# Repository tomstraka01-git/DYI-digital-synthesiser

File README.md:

# DYI digital synthesiser

## What is it?
It is a digital synthesizer fully made by me. It has 4 buttons and 5 controllable analog knobs to change settings. It can produce polyphonic sound and can connect to midi. It has settings like frequency, detune, volume, filters, chorus, delay, lfo, etc. It has two 2 watt speakers to produce sound and fully made by me pcb.

## Why?
I have always liked music, since i was kid i played piano, so i wanted to connect my interest in electronics and music into one project. That is why i  made this synthesizer. It has taught me about digital sound and audio alot.

## Electronics
The project uses custom pcb and some modules. It uses PCM5102 I2S audio module for sound generation and PAM8403 for sound amplifying, before it goes into 2040 8 ohm 2 watt speakers. It uses pico 2 as a microcontroller that does all the calculations etc. The pcb is going to be made by jlcpcb and it is fully opensource. It uses voltage dividers for battery percent readings, diode and a fast fuse for safety protection.

## Case
I wont use a case for the synthesizer, it will all be on the pcb and few things wich are not on it, like battery are gonna be held there with zip ties and other things.

| Name | Purpose | Quantity | Total Cost (USD) | Link | Distributor |
|:---|:---|-----------:|-------------------:|:---|:---|
| Custom JLCPCB PCB | A custom pcb connecting parts together. | 1 | 6.9 | https://cart.jlcpcb.com/quote?stencilLayer=2&stencilWidth=100&stencilLength=100&stencilCounts=5&plateType=1&spm=Jlcpcb.Homepage.1010 | JLCPCB |
| Raspberry Pi Pico W | Microcontroller, the brain of the synthesizer. | 1 | 11.0 | https://www.laskakit.cz/raspberry-pi-pico-w/ | laskakit.cz |
| 2040 speaker 2 watt 8 ohm | Speaker for producing audio. | 2 | 1.06 | https://www.lcsc.com/product-detail/C50387229.html?s_z=n_q_XHXDZ%25202040T-8%25CE%25A92W&spm=wm.fly.bg.0.xh&lcsc_vid=FVNfUlUEFAVYXgBSFAcKAVJRQwIPUFRWFFBeV1deT1gxVlNeR1VWVl1TQFdYUjsOAxUeFF5JWBYZEEoKFBINSQcJGk4eFQsCAgIaSgADAwAHC0slQlFdX1NURFFADxALGw%3D%3D | lcsc |
| GY-PCM5102 I2S audio module | Audio generator, wich then passes audio to the amplifier | 1 | 4.71 | https://www.laskakit.cz/gy-pcm5102-i2s-audio-modul/ | laskakit.cz |
| DuPont pins Female 40pin | Female dupont pins for pico 2. | 1 | 0.34 | https://dratek.cz/arduino-platforma/913-dupont-dutinkova-lista-samice-samec.html | Dratek.cz |
| Diode 1N5822 | Diode for reverse battery protection. 10 is minimum quantity. | 5 | 1.19 | https://www.lcsc.com/product-detail/schottky-diodes_stmicroelectronics-1n5822_C915962.html | lcsc |
| Button, 6 x 6 x 6 mm | Button for changing things in menu. | 4 | 0.39 | https://dratek.cz/arduino-platforma/1253-mikrospinac-6x6x6-mm-tlacitko.html | Dratek.cz |
| 5 $\times$ 20 GLASS QUICK BLOW FUSE 3A | Fast blow fuse for safety in the pcb. | 10 | 0.59 | https://www.lcsc.com/product-detail/Glass-Fuses_3A-250VAC_C3118.html | lcsc |
| 5 $\times$ 20mm fuse holder, PCB THT | Fuse holder. Holds the fuse, 20 is the minimum quantity. | 5 | 0.4 | https://www.lcsc.com/product-detail/C3131.html?s_z=n_q_5x20%2520BLX-A&spm=wm.fly.bg.0.xh&lcsc_vid=FVNfUlUEFAVYXgBSFAcKAVJRQwIPUFRWFFBeV1deT1gxVlNeR1VWVlNSR1ddVTsOAxUeFF5JWBYZEEoKFBINSQcJGk4dAgUUFAk%3D | lcsc |
| Metalized rezistor 100K - 0,25W 1% | Resistor for voltage divider. | 2 | 0.1 | https://dratek.cz/arduino-platforma/7653-rezistor-100k-0.25-w-1.html | Dratek.cz |
| Metalized rezistor 330K - 0,25W 1% | Resistor for voltage divider. | 4 | 0.19 | https://dratek.cz/arduino-platforma/174965-metalizovany-rezistor-330k-0-25w-1.html | Dratek.cz |
| Condensator  50v 100microfarad | Condensator for power smoothing. | 4 | 0.19 | https://dratek.cz/arduino-platforma/7825-kondenzator-100uf-50v.html | Dratek.cz |
| POT 10k$\Omega$ Through Hole | Potenciometer for the knobs in the synthesizer. Used to control value and settings. | 10 | 6.92 | https://www.lcsc.com/product-detail/C209779.html?s_z=n_q_C209779&globalKeyword=C209779 | lcsc |
| JST S2B-PH-K-S | The jst pin for battery. 20 is the minimum quantity | 20 | 0.76 | https://www.lcsc.com/product-detail/Wire-To-Board-Wire-To-Wire-Connector_JST-S2B-PH-K-S-LF-SN_C173752.html | lcsc |
| MICROCHIP MCP3208-CI/P | analog multiplexer to read potencimeters, because pico does not have enough adc pins | 1 | 4.27 | https://www.lcsc.com/product-detail/C1543277.html?s_z=n_q_MCP3208&spm=wm.fly.bg.4.xh&lcsc_vid=FVNfUlUEFAVYXgBSFAcKAVJRQwIPUFRWFFBeV1deT1gxVlNeR1JfUVFWTlhdVjsOAxUeFF5JWBYZEEoKFBINSQcJGk4eFQsCAgIaSgADAwAHC0snGQACCANLIw5DIw0BHhUPC0klGA8YAhYSEhMdSiUiNBIxKi0lJS4tLy02KCwtN1dUR1lDJC1LJC0xKic2RFNeXzslRldXVF1IHxUDCw%3D%3D | lcsc |
| 2.54mm 16P DIP Tin Square Hole 7.62mm DIP-16 IC Sockets RoHS | Holder for the MCP3208 chip. 10 is the minimum quantity on lcsc. | 10 | 0.48 | https://www.lcsc.com/product-detail/IC-Sockets_BOOMELE-Boom-Precision-Elec-C2326_C2326.html | lcsc |
| Digital audio amplifier PAM8403 - 2 x 3W | To amplify the sound generated by the PCM5102A for speakers | 1 | 0.67 | https://dratek.cz/arduino-platforma/953-audio-zesilovac-2x3w.html | Dratek.cz |
| IIC I2C OLED displej 1,3" - White, 128 x 64 | Oled display for vizualization of the sound and values. Allows the user to see what vaues he is setting and what mode is he on. | 1 | 8.01 | https://dratek.cz/arduino-platforma/3181-iic-i2c-oled-1-3-displej-128x64-bily.html | Dratek.cz |

Total shipping: $34

Total price: $86

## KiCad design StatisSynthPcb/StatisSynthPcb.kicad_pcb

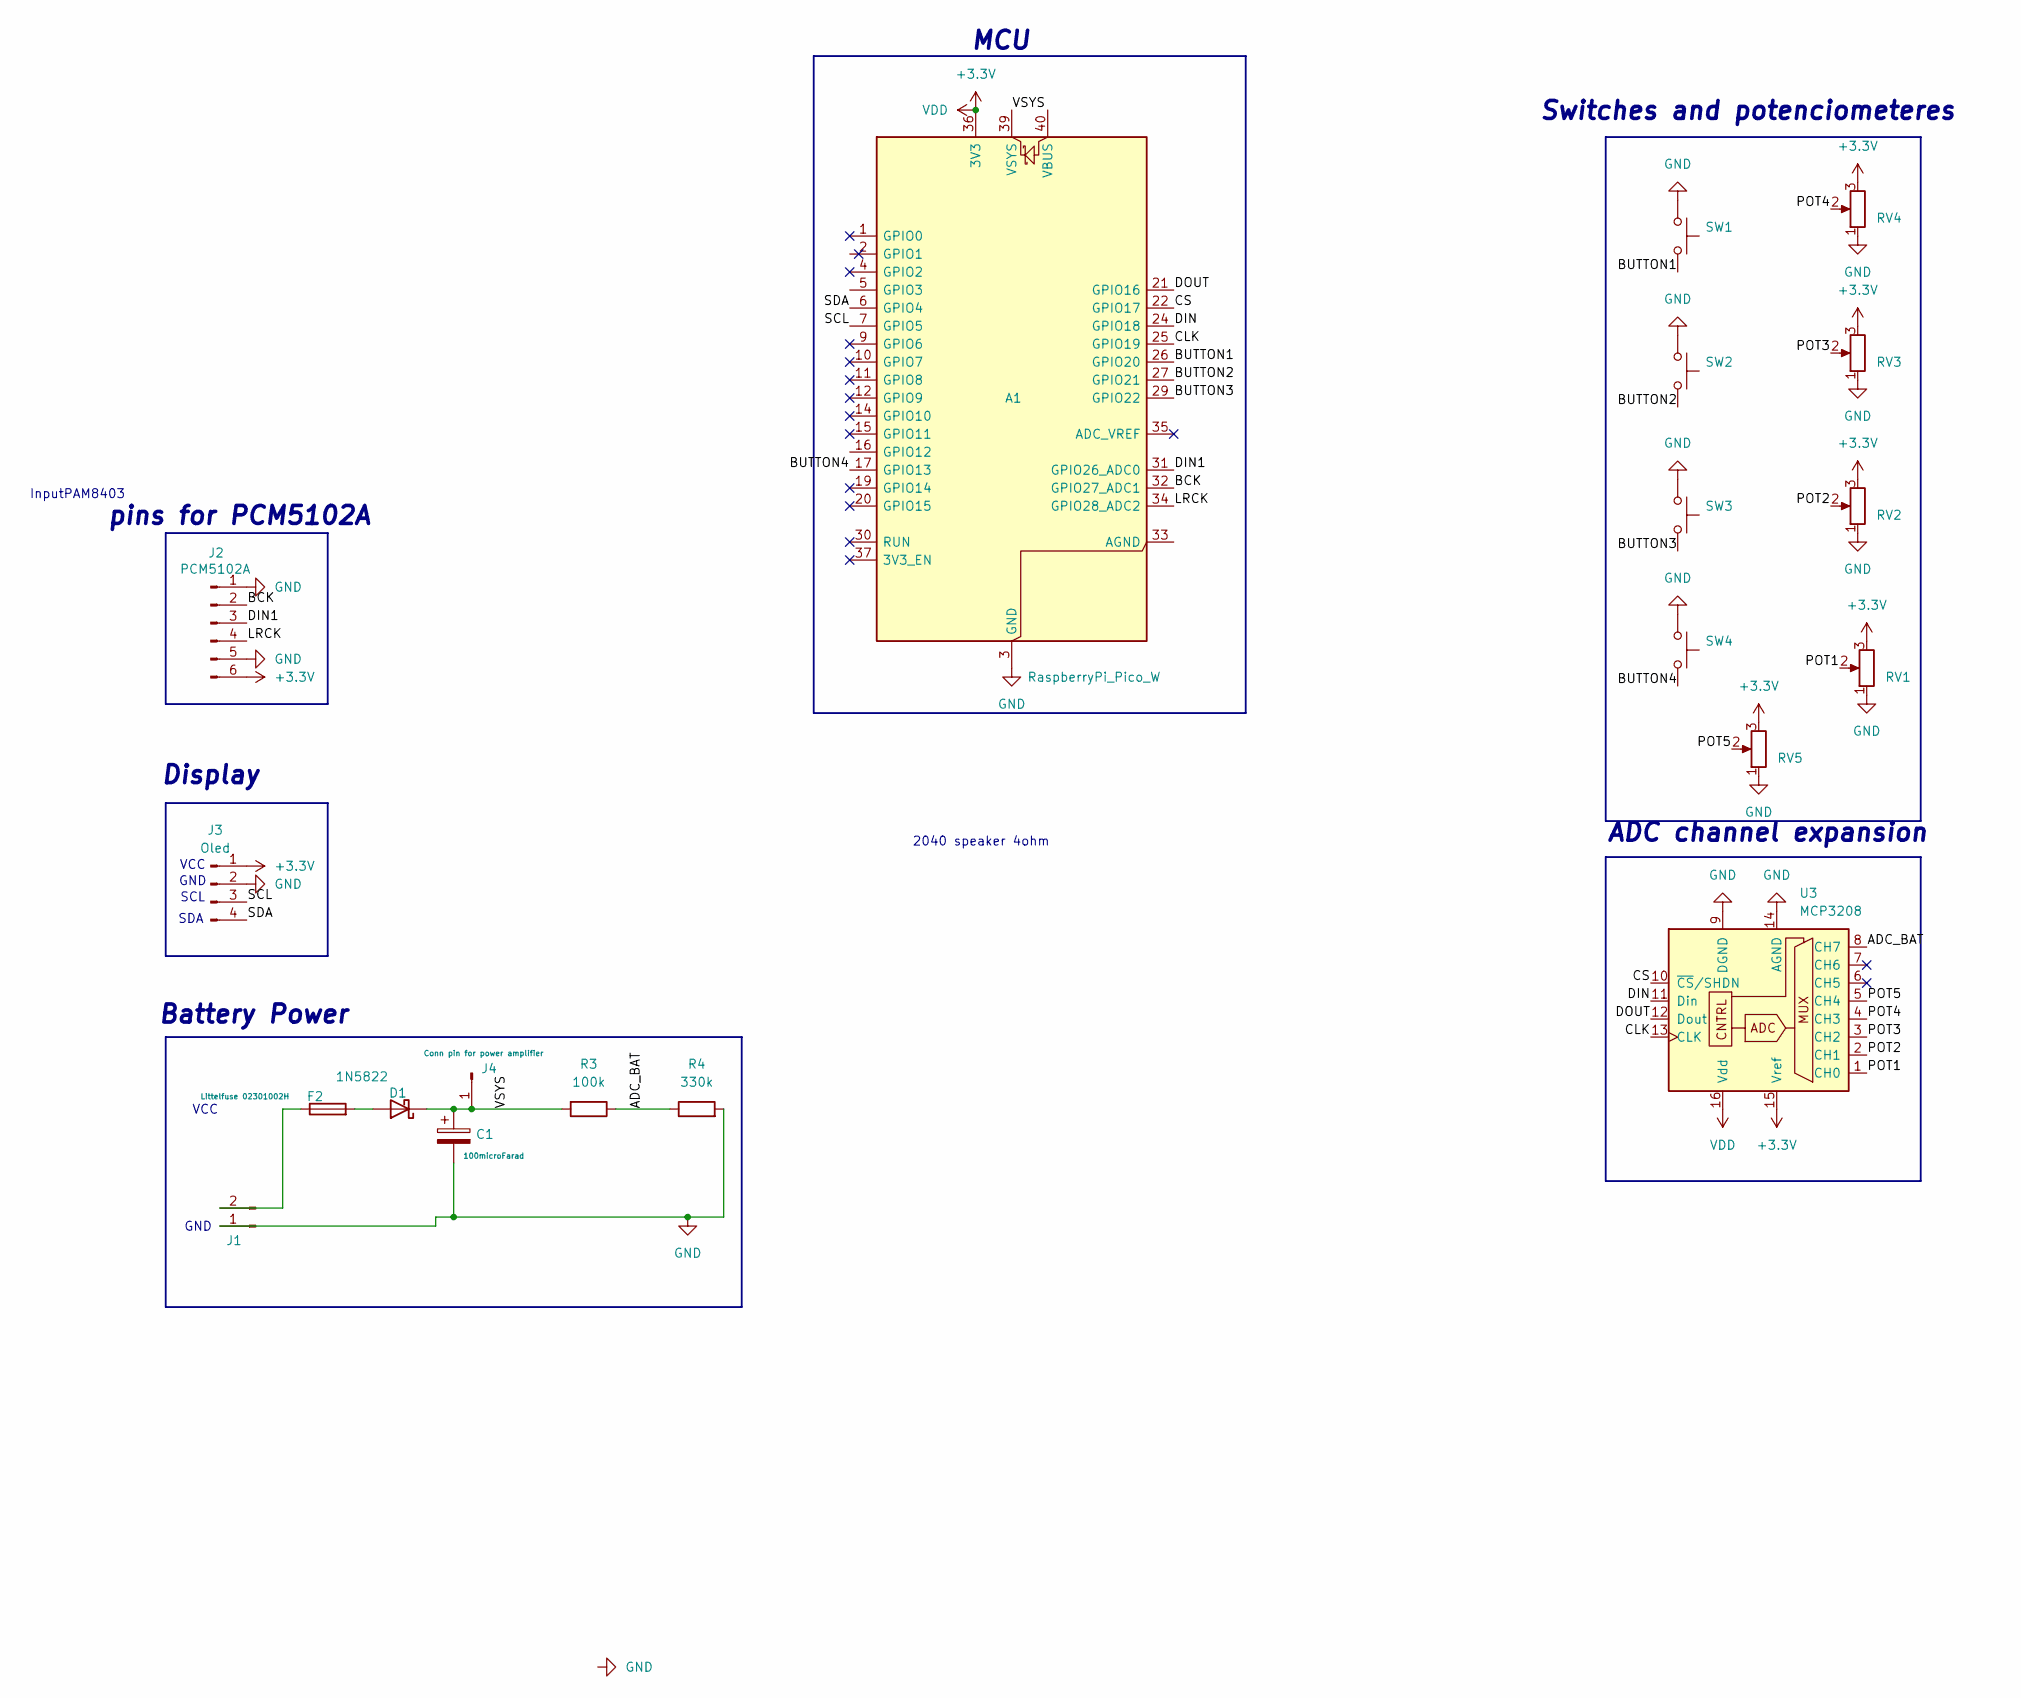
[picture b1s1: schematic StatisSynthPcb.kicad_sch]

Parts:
A1: RaspberryPi_Pico_W; RaspberryPi_Pico_Common
C1: 100microFarad; CP_Radial_D6.3mm_P2.50mm
D1: 1N5822; D_DO-201AD_P15.24mm_Horizontal
F2: Littelfuse 02301002H; Fuseholder_Cylinder-5x20mm_Schurter_0031_8201_Horizontal_Op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
J1: Conn_01x02_Pin; JST_PH_S2B-PH-K_1x02_P2.00mm_Horizontal
J2: PCM5102A; PinSocket_1x06_P2.54mm_Vertical
J3: Oled; PinSocket_1x04_P2.54mm_Vertical
J4: Conn pin for power amplifier; PinSocket_1x01_P2.54mm_Vertical
R3: 100k; R_Axial_DIN0207_L6.3mm_D2.5mm_P7.62mm_Horizontal
R4: 330k; R_Axial_DIN0207_L6.3mm_D2.5mm_P7.62mm_Horizontal
RV1, RV2, RV3, RV4, RV5: R_Potentiometer; Potentiometer_Alps_RK09K_Single_Vertical
SW1, SW2, SW3, SW4: SW_Push; SW_PUSH_6mm
U3: MCP3208; DIP-16_W7.62mm_Socket_LongPads

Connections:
+3.3V: A1.36 (3V3), J2.6, J3.1, RV1.3, RV2.3, RV3.3, RV4.3, RV5.3, U3.15 (Vref), U3.16 (Vdd)
/ADC_BAT: R3.1, R4.1, U3.8 (CH7)
/BCK: A1.32 (GPIO27_ADC1), J2.2
/BUTTON1: A1.26 (GPIO20), SW1.2
/BUTTON2: A1.27 (GPIO21), SW2.2
/BUTTON3: A1.29 (GPIO22), SW3.2
/BUTTON4: A1.17 (GPIO13), SW4.2
/CLK: A1.25 (GPIO19), U3.13 (CLK)
/CS: A1.22 (GPIO17), U3.10 (~CS/SHDN)
/DIN: A1.24 (GPIO18), U3.11 (Din)
/DIN1: A1.31 (GPIO26_ADC0), J2.3
/DOUT: A1.21 (GPIO16), U3.12 (Dout)
/LRCK: A1.34 (GPIO28_ADC2), J2.4
/POT1: RV1.2, U3.1 (CH0)
/POT2: RV2.2, U3.2 (CH1)
/POT3: RV3.2, U3.3 (CH2)
/POT4: RV4.2, U3.4 (CH3)
/POT5: RV5.2, U3.5 (CH4)
/SCL: A1.7 (GPIO5), J3.3
/SDA: A1.6 (GPIO4), J3.4
/VSYS: A1.39 (VSYS), C1.1, D1.1 (K), J4.1 (Pin_1_1), R3.2
GND: A1.3 (GND), A1.8 (GND), A1.13 (GND), A1.18 (GND), A1.23 (GND), A1.28 (GND), A1.38 (GND), C1.2, J1.1, J2.1, J2.5, J3.2, R4.2, RV1.1, RV2.1, RV3.1, RV4.1, RV5.1, SW1.1, SW2.1, SW3.1, SW4.1, U3.9 (DGND), U3.14 (AGND)
unnamed: D1.2 (A), F2.2
unnamed: F2.1, J1.2

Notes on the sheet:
Battery Power
ADC channel expansion
SCL
VCC
InputPAM8403
GND
pins for PCM5102A
SDA
Switches and potenciometeres
GND
Display
2040 speaker 4ohm
MCU

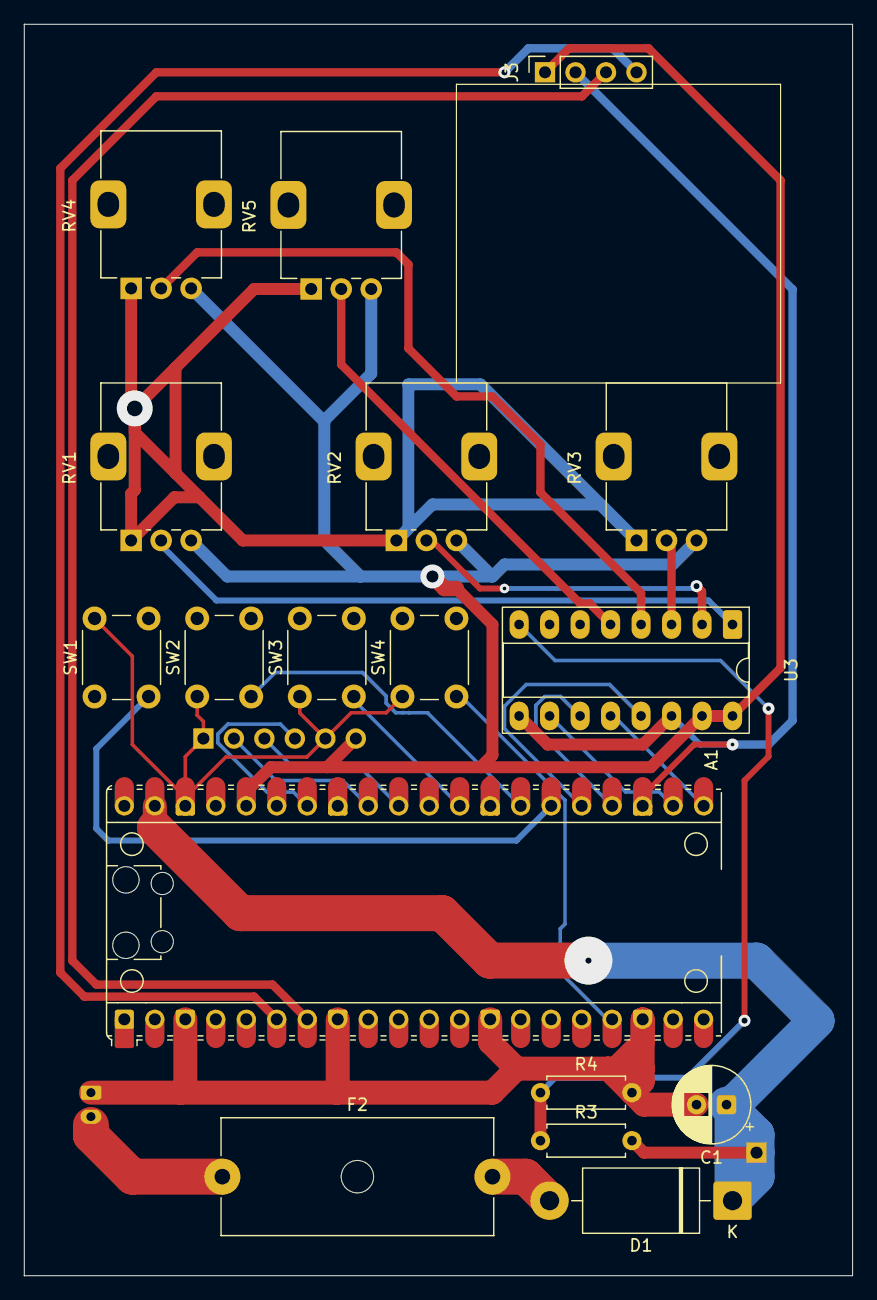
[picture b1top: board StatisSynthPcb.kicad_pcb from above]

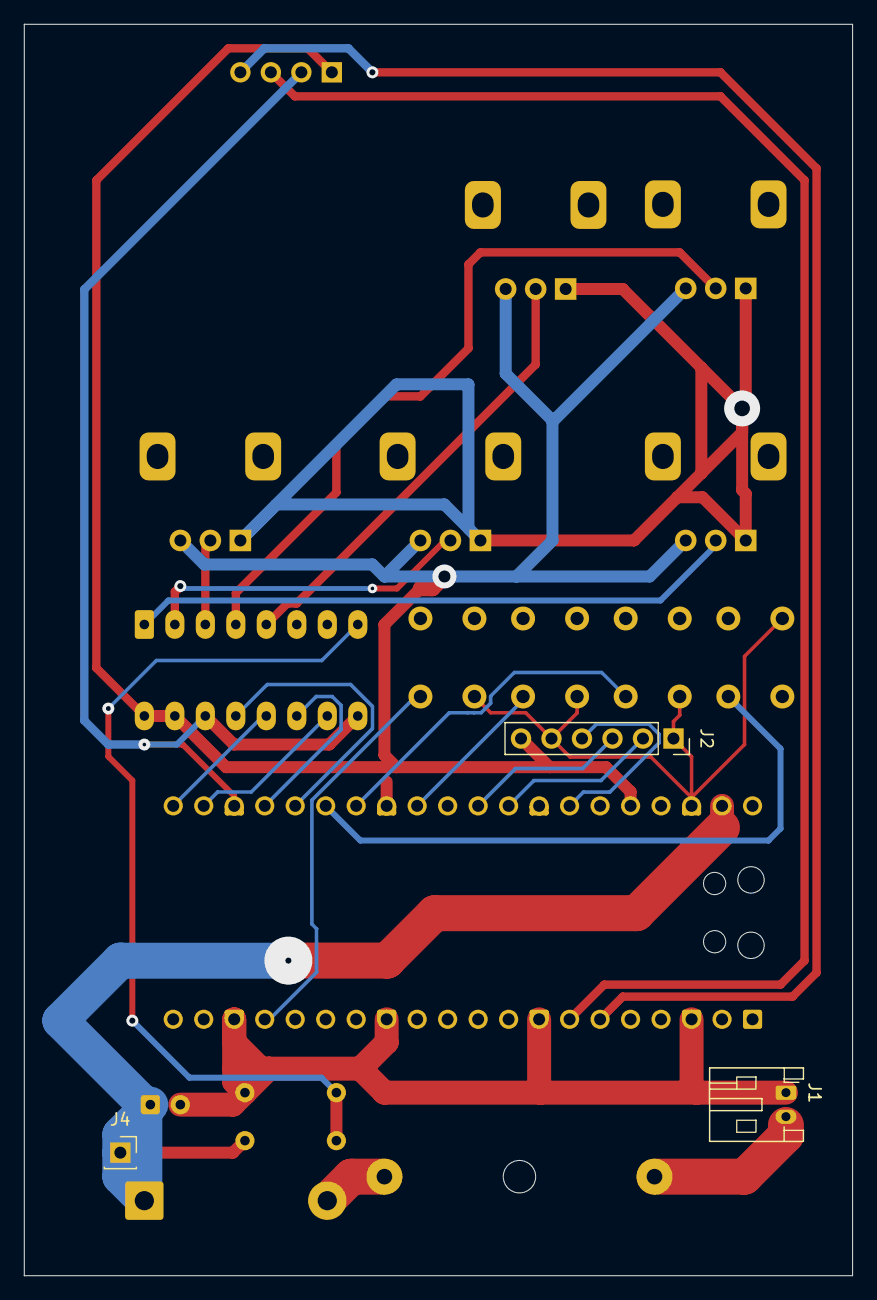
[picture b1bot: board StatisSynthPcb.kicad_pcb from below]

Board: 2 copper layers, 69.0 x 104.2 mm, 20 parts (3 on the bottom side), 24 nets.

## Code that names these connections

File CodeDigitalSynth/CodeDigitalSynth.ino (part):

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
#include "hardware/sync.h"

#define LRCK_PIN  28   
#define BCK_PIN   27   
#define DIN_PIN   26   

#define SAMPLE_RATE 44100
#define AMPLITUDE   32767
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#define MCP_DIN   18   
#define MCP_CLK   19

#define BUTTON1 20 // OSC1 waveform cycle
#define BUTTON2 21 // Sound ON/OFF
#define BUTTON3 22 // Mode cycle
#define BUTTON4 13 // OSC2 waveform cycle  ← now used


#define SCREEN_WIDTH 128
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void setup() {
  USBDevice.begin();

  pinMode(BUTTON1, INPUT_PULLUP);
  pinMode(BUTTON2, INPUT_PULLUP);
  pinMode(BUTTON3, INPUT_PULLUP);
  pinMode(BUTTON4, INPUT_PULLUP);

  SPI.setRX(MCP_DOUT);
  SPI.setTX(MCP_DIN);
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  SPI.begin();
  mcp.begin(MCP_CS);
  
  i2s.setBCLK(BCK_PIN);   
  i2s.setDATA(DIN_PIN);  
  i2s.setLRCLK(LRCK_PIN);
  i2s.setBitsPerSample(16);
  i2s.begin(SAMPLE_RATE);

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
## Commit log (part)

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2026-04-30 made first pcb version
2026-05-10 change in schematic
2026-05-11 code change
2026-05-13 added to code synth idk
2026-05-14 added resonance filter
2026-05-14 added other oscillator and core
2026-05-15 added oled display
2026-05-20 changed pcb fuse, diode etc
2026-05-21 chnages to code and pcb
2026-06-02 pcb change
2026-06-03 added photos
2026-06-03 added gerbers photos bom
2026-06-03 added step
